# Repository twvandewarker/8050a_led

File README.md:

# 8050a_led

Work in progress - Replacing the LCD display in a Fluke 8050A bench multimeter with 7 segment LED displays.

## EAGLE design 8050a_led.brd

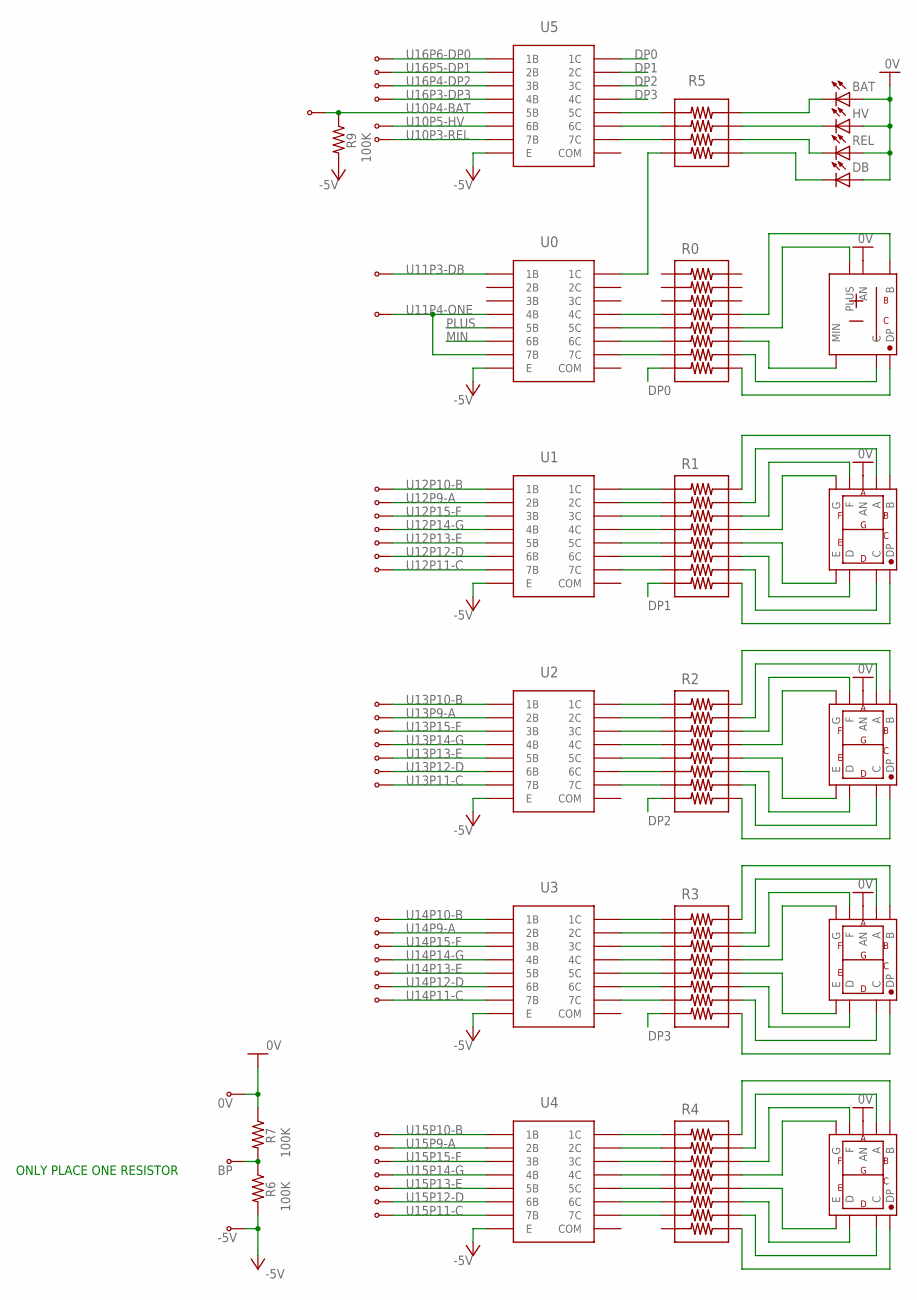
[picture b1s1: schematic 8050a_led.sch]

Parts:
BAT: LED_0805; 0805_POL
D0: LUMEX_LDF-A5616RI; LUMEX_LDS-A516RI
D1, D2, D3, D4: LUMEX_LDS-A516RI
DB: LED_0805; 0805_POL
HV: LED_0805; 0805_POL
R0, R1, R2, R3, R4: BOURNS_CAT16-XXXJ8; BOURNS_CAT16-J8
R5: BOURNS_CAT16XXXJ4; BOURNS_CAT16-J4
R6, R7, R9: 100K; 0603
REL: LED_0805; 0805_POL
TP1, TP2, TP3, TP4, TP5, TP6, TP7, TP8, TP9, TP10, TP11, TP12, TP13, TP14, TP15, TP16, TP17, TP18, TP19, TP20, TP21, TP22, TP23, TP24, TP25, TP26, TP27, TP28, TP29, TP30, TP31, TP32, TP35, TP36, TP37, TP38, TP39, TP40, TP41, TP42: KEYSTONE_500X
U0, U1, U2, U3, U4, U5: TI_ULN2003A; SOIC16_TI

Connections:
0V: BAT.P$1 (A), D0.P$3 (AN), D0.P$8 (AN), D1.P$3 (AN), D1.P$8 (AN), D2.P$3 (AN), D2.P$8 (AN), D3.P$3 (AN), D3.P$8 (AN), D4.P$3 (AN), D4.P$8 (AN), DB.P$1 (A), HV.P$1 (A), R7.P$1 (1), REL.P$1 (A), TP9.P$1
-5V: R6.P$2 (2), R9.P$2 (2), TP8.P$1, U0.P$8 (E), U1.P$8 (E), U2.P$8 (E), U3.P$8 (E), U4.P$8 (E), U5.P$8 (E)
BP: R6.P$1 (1), R7.P$2 (2), TP35.P$1
DP0: R0.P$8, U5.P$16 (1C)
DP1: R1.P$8, U5.P$15 (2C)
DP2: R2.P$8, U5.P$14 (3C)
DP3: R3.P$8, U5.P$13 (4C)
MIN: U0.P$6 (6B)
unnamed: R1.P$1, U1.P$16 (1C)
unnamed: R1.P$2, U1.P$15 (2C)
unnamed: R1.P$3, U1.P$14 (3C)
unnamed: R1.P$4, U1.P$13 (4C)
unnamed: R1.P$5, U1.P$12 (5C)
unnamed: R1.P$6, U1.P$11 (6C)
unnamed: R1.P$7, U1.P$10 (7C)
unnamed: D1.P$6 (B), R1.P$16
unnamed: D1.P$7 (A), R1.P$15
unnamed: D1.P$9 (F), R1.P$14
unnamed: D1.P$10 (G), R1.P$13
unnamed: D1.P$1 (E), R1.P$12
unnamed: D1.P$2 (D), R1.P$11
unnamed: D1.P$4 (C), R1.P$10
unnamed: D1.P$5 (DP), R1.P$9
unnamed: R2.P$1, U2.P$16 (1C)
unnamed: R2.P$2, U2.P$15 (2C)
unnamed: R2.P$3, U2.P$14 (3C)
unnamed: R2.P$4, U2.P$13 (4C)
unnamed: R2.P$5, U2.P$12 (5C)
unnamed: R2.P$6, U2.P$11 (6C)
unnamed: R2.P$7, U2.P$10 (7C)
unnamed: D2.P$6 (B), R2.P$16
unnamed: D2.P$7 (A), R2.P$15
unnamed: D2.P$9 (F), R2.P$14
unnamed: D2.P$10 (G), R2.P$13
unnamed: D2.P$1 (E), R2.P$12
unnamed: D2.P$2 (D), R2.P$11
unnamed: D2.P$4 (C), R2.P$10
unnamed: D2.P$5 (DP), R2.P$9
unnamed: R3.P$1, U3.P$16 (1C)
unnamed: R3.P$2, U3.P$15 (2C)
unnamed: R3.P$3, U3.P$14 (3C)
unnamed: R3.P$4, U3.P$13 (4C)
unnamed: R3.P$5, U3.P$12 (5C)
unnamed: R3.P$6, U3.P$11 (6C)
unnamed: R3.P$7, U3.P$10 (7C)
unnamed: D3.P$6 (B), R3.P$16
unnamed: D3.P$7 (A), R3.P$15
unnamed: D3.P$9 (F), R3.P$14
unnamed: D3.P$10 (G), R3.P$13
unnamed: D3.P$1 (E), R3.P$12
unnamed: D3.P$2 (D), R3.P$11
unnamed: D3.P$4 (C), R3.P$10
unnamed: D3.P$5 (DP), R3.P$9
unnamed: R4.P$1, U4.P$16 (1C)
unnamed: R4.P$2, U4.P$15 (2C)
unnamed: R4.P$3, U4.P$14 (3C)
unnamed: R4.P$4, U4.P$13 (4C)
unnamed: R4.P$5, U4.P$12 (5C)
unnamed: R4.P$6, U4.P$11 (6C)
unnamed: R4.P$7, U4.P$10 (7C)
unnamed: D4.P$6 (B), R4.P$16
unnamed: D4.P$7 (A), R4.P$15
unnamed: D4.P$9 (F), R4.P$14
unnamed: D4.P$10 (G), R4.P$13
unnamed: D4.P$1 (E), R4.P$12
unnamed: D4.P$2 (D), R4.P$11
unnamed: D4.P$4 (C), R4.P$10
unnamed: D4.P$5 (DP), R4.P$9
unnamed: R0.P$7, U0.P$10 (7C)
unnamed: R0.P$6, U0.P$11 (6C)
unnamed: R0.P$5, U0.P$12 (5C)
unnamed: R5.P$3, U5.P$10 (7C)
unnamed: R5.P$2, U5.P$11 (6C)
unnamed: R5.P$1, U5.P$12 (5C)
unnamed: R5.P$4, U0.P$16 (1C)
unnamed: R0.P$4, U0.P$13 (4C)
unnamed: HV.P$2 (C), R5.P$7
unnamed: R5.P$6, REL.P$2 (C)
unnamed: DB.P$2 (C), R5.P$5
unnamed: BAT.P$2 (C), R5.P$8
unnamed: D0.P$9 (PLUS), R0.P$12
unnamed: D0.P$6 (B), R0.P$13
unnamed: D0.P$1 (MIN), R0.P$11
unnamed: D0.P$4 (C), R0.P$10
unnamed: D0.P$5 (DP), R0.P$9
PLUS: U0.P$5 (5B)
U10P3-REL: TP42.P$1, U5.P$7 (7B)
U10P4-BAT: R9.P$1 (1), TP40.P$1, U5.P$5 (5B)
U10P5-HV: TP41.P$1, U5.P$6 (6B)
U11P3-DB: TP32.P$1, U0.P$1 (1B)
U11P4-ONE: TP31.P$1, U0.P$4 (4B), U0.P$7 (7B)
U12P9-A: TP2.P$1, U1.P$2 (2B)
U12P10-B: TP1.P$1, U1.P$1 (1B)
U12P11-C: TP7.P$1, U1.P$7 (7B)
U12P12-D: TP6.P$1, U1.P$6 (6B)
U12P13-E: TP5.P$1, U1.P$5 (5B)
U12P14-G: TP4.P$1, U1.P$4 (4B)
U12P15-F: TP3.P$1, U1.P$3 (3B)
U13P9-A: TP11.P$1, U2.P$2 (2B)
U13P10-B: TP10.P$1, U2.P$1 (1B)
U13P11-C: TP16.P$1, U2.P$7 (7B)
U13P12-D: TP15.P$1, U2.P$6 (6B)
U13P13-E: TP14.P$1, U2.P$5 (5B)
U13P14-G: TP13.P$1, U2.P$4 (4B)
U13P15-F: TP12.P$1, U2.P$3 (3B)
U14P9-A: TP18.P$1, U3.P$2 (2B)
U14P10-B: TP17.P$1, U3.P$1 (1B)
U14P11-C: TP23.P$1, U3.P$7 (7B)
U14P12-D: TP22.P$1, U3.P$6 (6B)
U14P13-E: TP21.P$1, U3.P$5 (5B)
U14P14-G: TP20.P$1, U3.P$4 (4B)
U14P15-F: TP19.P$1, U3.P$3 (3B)
U15P9-A: TP25.P$1, U4.P$2 (2B)
U15P10-B: TP24.P$1, U4.P$1 (1B)
U15P11-C: TP30.P$1, U4.P$7 (7B)
U15P12-D: TP29.P$1, U4.P$6 (6B)
U15P13-E: TP28.P$1, U4.P$5 (5B)
U15P14-G: TP27.P$1, U4.P$4 (4B)
U15P15-F: TP26.P$1, U4.P$3 (3B)
U16P3-DP3: TP39.P$1, U5.P$4 (4B)
U16P4-DP2: TP38.P$1, U5.P$3 (3B)
U16P5-DP1: TP37.P$1, U5.P$2 (2B)
U16P6-DP0: TP36.P$1, U5.P$1 (1B)

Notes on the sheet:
ONLY PLACE ONE RESISTOR

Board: 2 copper layers, 64 parts (0 on the bottom side), 121 nets, no tracks yet.
